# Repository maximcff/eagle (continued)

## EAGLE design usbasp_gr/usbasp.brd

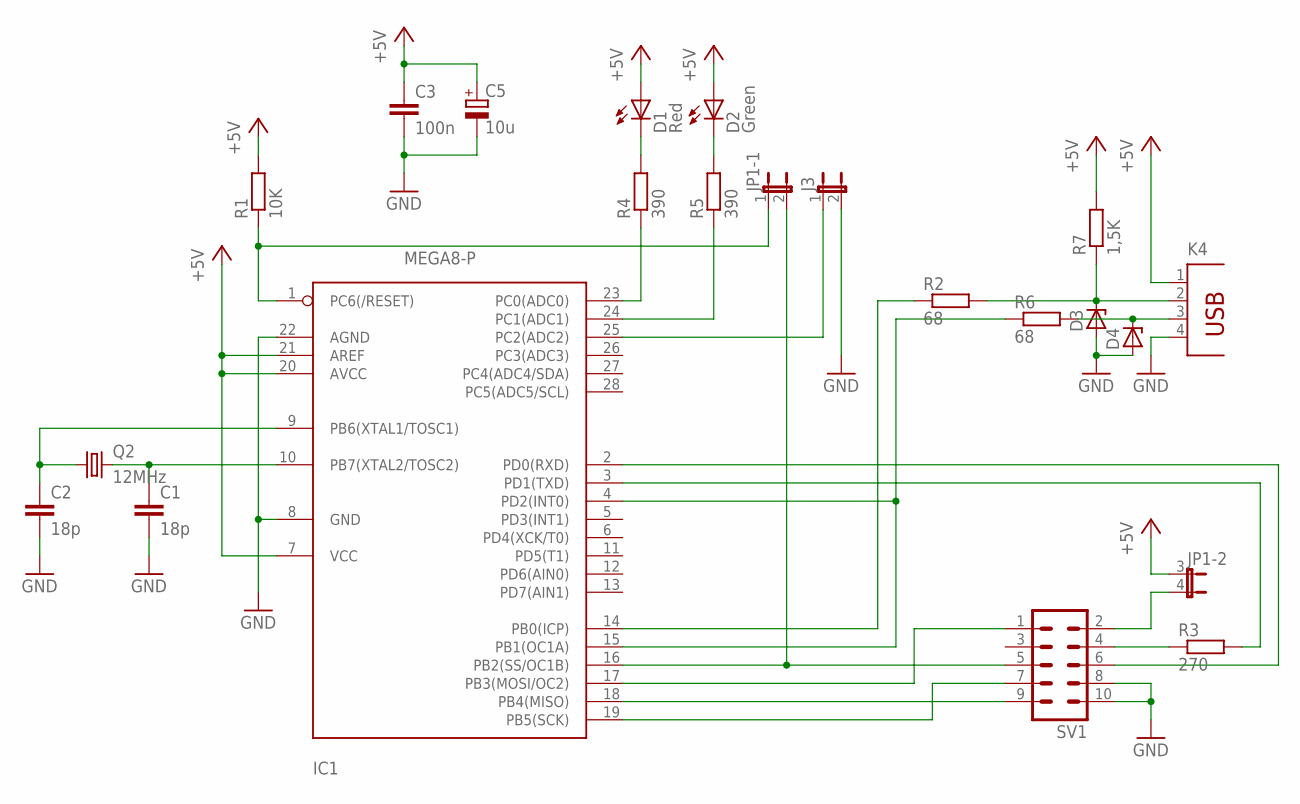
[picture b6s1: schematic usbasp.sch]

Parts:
C1, C2: 18p; C025-024X044
C3: 100n; C7.5B3
C5: 10u; E2,5-5
D1: Red; LED5MM
D2: Green; LED5MM
D3: ZENER-DIODEZD-5; ZDIO-5
D4: ZENER-DIODEZD-2.5; ZDIO-2.5
IC1: MEGA8-P; DIL28-3
J3: JP1E; JP1
JP1: JP2QE; JP2Q
K4: PN87520
Q2: 12MHz; HC49/S
R1: 10K; 0207/10
R2, R6: 68; 0207/10
R3: 270; 0207/10
R4, R5: 390; 0207/10
R7: 1,5K; 0207/10
SV1: ML10

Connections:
+5V: C3.1, C5.+, D1.A, D2.A, IC1.7 (VCC), IC1.20 (AVCC), IC1.21 (AREF), JP1.3 (1), K4.1, R1.2, R7.2
GND: C1.2, C2.2, C3.2, C5.-, D3.A, D4.A, IC1.8 (GND), IC1.22 (AGND), J3.2, K4.4, SV1.8, SV1.10
unnamed: D3.C, K4.2, R2.2, R7.1
unnamed: D4.C, K4.3, R6.2
unnamed: C1.1, IC1.10 (PB7(XTAL2/TOSC2)), Q2.2
unnamed: C2.1, IC1.9 (PB6(XTAL1/TOSC1)), Q2.1
unnamed: JP1.4 (2), SV1.2
unnamed: R3.1, SV1.4
unnamed: IC1.3 (PD1(TXD)), R3.2
unnamed: IC1.2 (PD0(RXD)), SV1.6
unnamed: IC1.17 (PB3(MOSI/OC2)), SV1.1
unnamed: IC1.19 (PB5(SCK)), SV1.7
unnamed: IC1.18 (PB4(MISO)), SV1.9
unnamed: IC1.16 (PB2(SS/OC1B)), JP1.2, SV1.5
unnamed: IC1.1 (PC6(/RESET)), JP1.1, R1.1
unnamed: IC1.14 (PB0(ICP)), R2.1
unnamed: IC1.25 (PC2(ADC2)), J3.1
unnamed: IC1.23 (PC0(ADC0)), R4.1
unnamed: IC1.24 (PC1(ADC1)), R5.1
unnamed: IC1.4 (PD2(INT0)), IC1.15 (PB1(OC1A)), R6.1
unnamed: D1.K (C), R4.2
unnamed: D2.K (C), R5.2

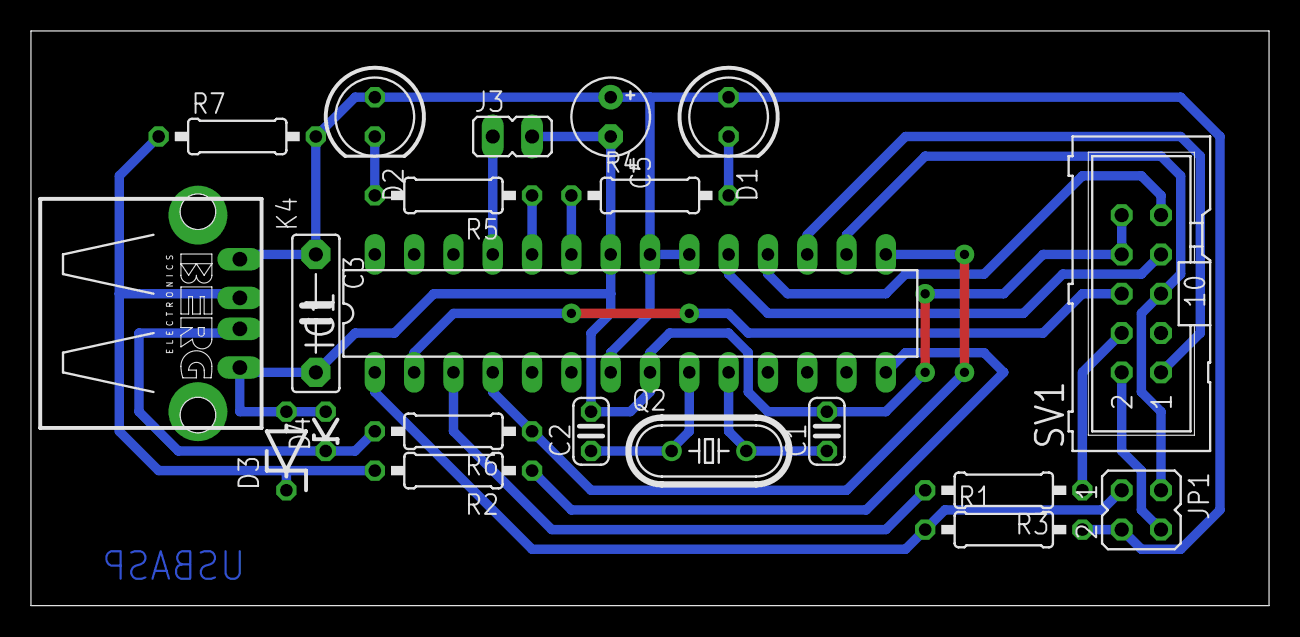
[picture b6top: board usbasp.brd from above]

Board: 2 copper layers, 80.0 x 37.1 mm, 21 parts (0 on the bottom side), 22 nets.

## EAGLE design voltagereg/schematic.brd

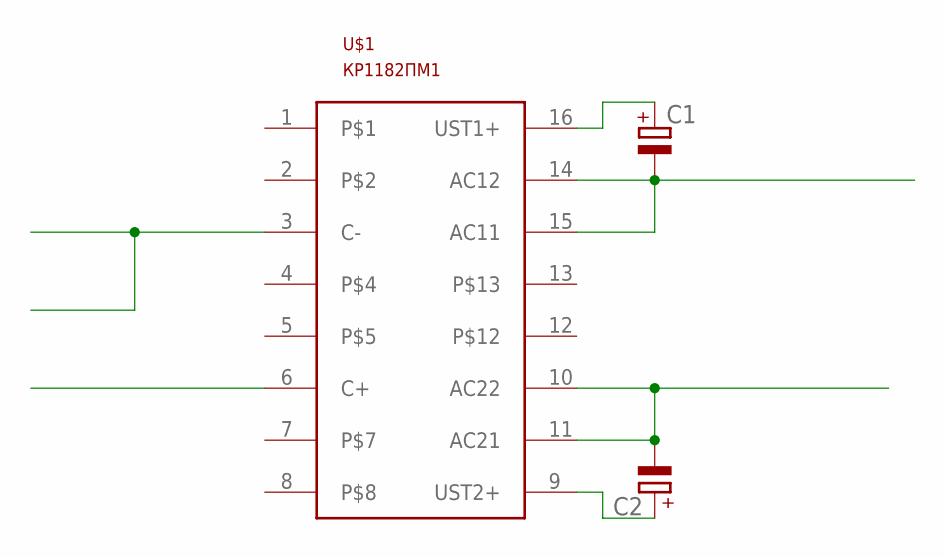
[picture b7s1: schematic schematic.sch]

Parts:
C1, C2: CPOL-EUE2.5-5; E2,5-5
U$1: КР1182ПМ1; DIL16

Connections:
unnamed: C1.-, U$1.14 (AC12), U$1.15 (AC11)
unnamed: C2.-, U$1.10 (AC22), U$1.11 (AC21)
unnamed: C1.+, U$1.16 (UST1+)
unnamed: C2.+, U$1.9 (UST2+)

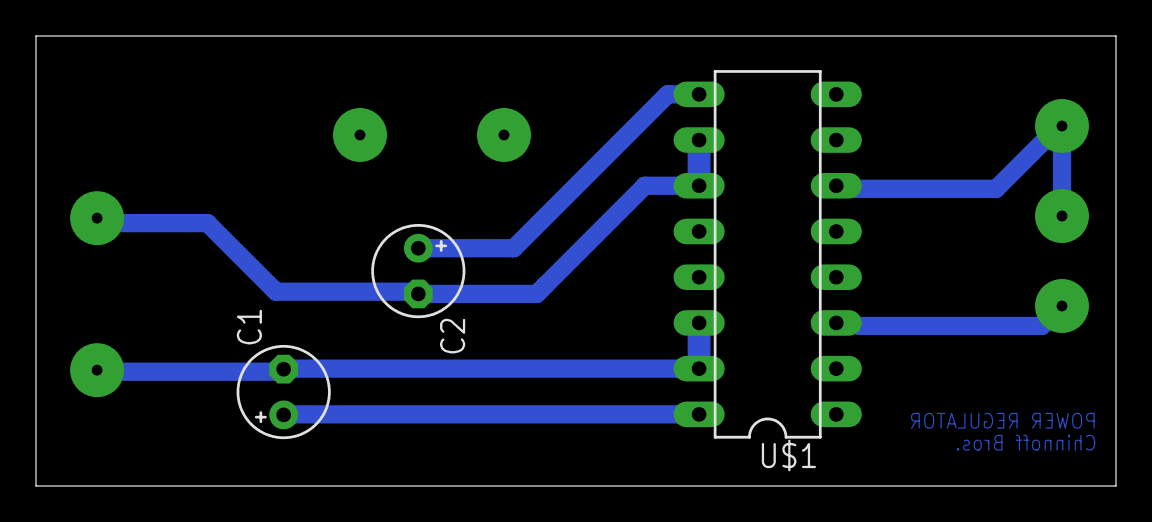
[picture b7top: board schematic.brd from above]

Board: 2 copper layers, 60.0 x 25.0 mm, 3 parts (0 on the bottom side), 4 nets.

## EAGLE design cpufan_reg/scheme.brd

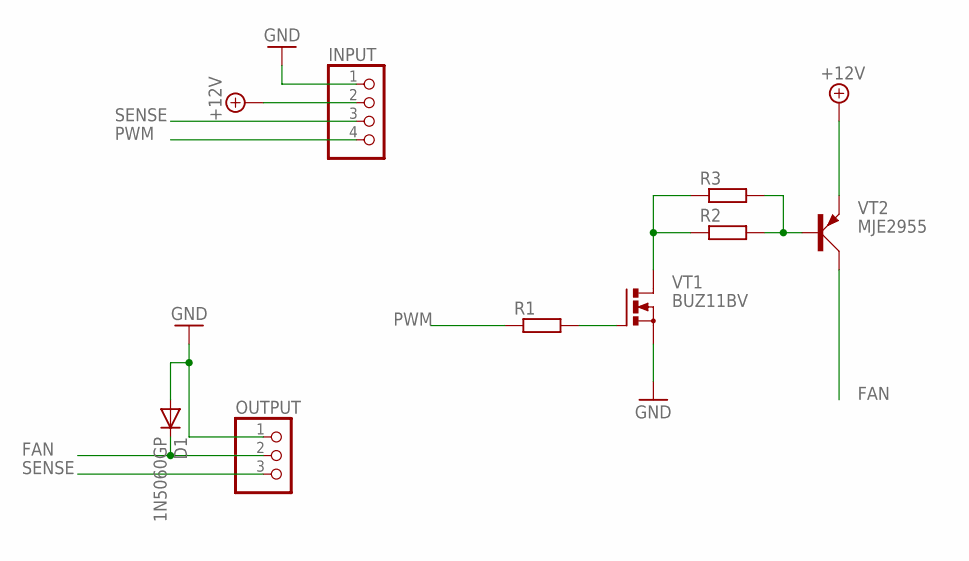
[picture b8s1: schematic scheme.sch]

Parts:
D1: 1N5060GP; DO15-12
INPUT: PINHD-1X4; 1X04
OUTPUT: PINHD-1X3; 1X03
R1: R-EU_0204/7; 0204/7
R2, R3: R-EU_0411/15; 0411/15
VT1: BUZ11BV; TO220BV
VT2: MJE2955; TO220AV

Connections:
+12V: INPUT.2, VT2.E
FAN: D1.C, OUTPUT.2, VT2.C
GND: D1.A, INPUT.1, OUTPUT.1, VT1.S
unnamed: R2.2, R3.2, VT2.B
unnamed: R2.1, R3.1, VT1.D
unnamed: R1.2, VT1.G
PWM: INPUT.4, R1.1
SENSE: INPUT.3, OUTPUT.3

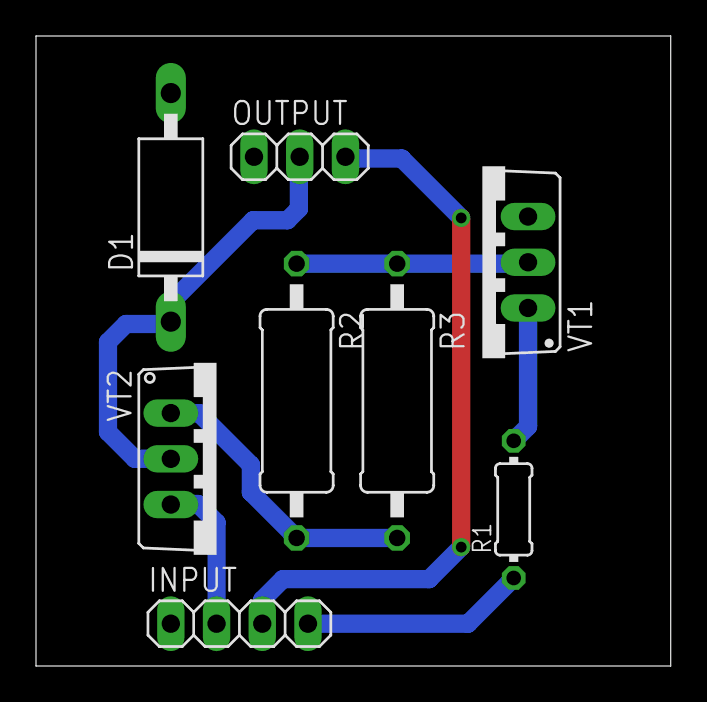
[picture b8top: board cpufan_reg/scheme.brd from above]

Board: 2 copper layers, 35.3 x 35.0 mm, 8 parts (0 on the bottom side), 8 nets.

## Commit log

2014-01-11 добавил старые проект из eagle, всякая ерунда:)
2014-05-17 добавил GPS-TRACKER-48 и DC-DC
2014-05-24 добавил 2x_stepper_driver -- драйвер 2х шаговых двигателей и 1 обычного. применяется в плоттере.
2014-05-27 почистил от всякого говна
2014-10-11 добавил mega168board
